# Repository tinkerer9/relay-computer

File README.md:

# Relay Computer
A relay computer that adds or subtracts two 4-bit numbers made for a Capstone project

## How to use
Power the computer with a 5V through the barrel jack on the top-right.

There are nine switches on the bottom left&mdash;these are the inputs.
The four on the top are the A3-A0 inputs, and the four on the bottom are the B3-B0 inputs.

On the the switch on the middle-right is the additon-subtraction selector.
Switch it up to add the two numbers, and down to subtract them.

## Bill of materials
Here is the BOM (bill of materials) for one of the computer, with links.
Prices are included (shipping not included) but always subject to change.

| Item | Variant | Quantity | Link | Price |
| :-: | :-: | :-: | :-: | :-: |
| Relays *(100x)* | SRD-05VDC-SLC | 20 | [AliExpress](https://www.aliexpress.us/item/3256805988664644.html) | $19.27 |
| Diodes *(100x)* | 1N4007 | 28 | [Amazon](https://www.amazon.com/dp/B0FC2CQF24) | $5.99 |
| LEDs | *red, 5mm* | 33 | | |
| Switches *(10x)* | MTS-102 | 9 | [Amazon](https://www.amazon.com/dp/B0799HC3VY) | $7.99 |
| Barrel Jack | *5.5mm OD* | 1 | | |
| Resistors | 220&ohm; | 33 | | |
| PCB *(5x)* | | 1 | *see [how to order](#how-to-order)* | $15.80 |
| **Total** | | **125** | | **$49.05** |

## How to order
Head to [JLCPCB](https://cart.jlcpcb.com/quote?stencilLayer=2&stencilWidth=140&stencilLength=210&plateType=1) and upload the gerber file at [`production.zip`](https://github.com/tinkerer9/relay-computer/raw/refs/heads/main/production.zip).

Use the default options for customizing your order.
Use this table for reference:

| Option | Selection |
| :-: | :-: |
| Base Material | FR-4 |
| Layers | 2 |
| Dimensions | 210 * 140 mm |
| PCB Qty | *you choose* |
| Product Type | Industrial/Consumer electronics |
| PCB Thickness | 1.6mm |
| PCB Color | *you choose* |

Select a build time and add the PCB to your cart.

For my order, the 5 PCBs costed **$15.80** and the shipping costed **&approx;$30**, plus tarrifs.
I ended up paying **&approx;$50**.
These prices are subject to change.

## Questions
For any questions about this project, feel free to create a [new issue](https://github.com/tinkerer9/relay-computer/issues/new) on this repository.

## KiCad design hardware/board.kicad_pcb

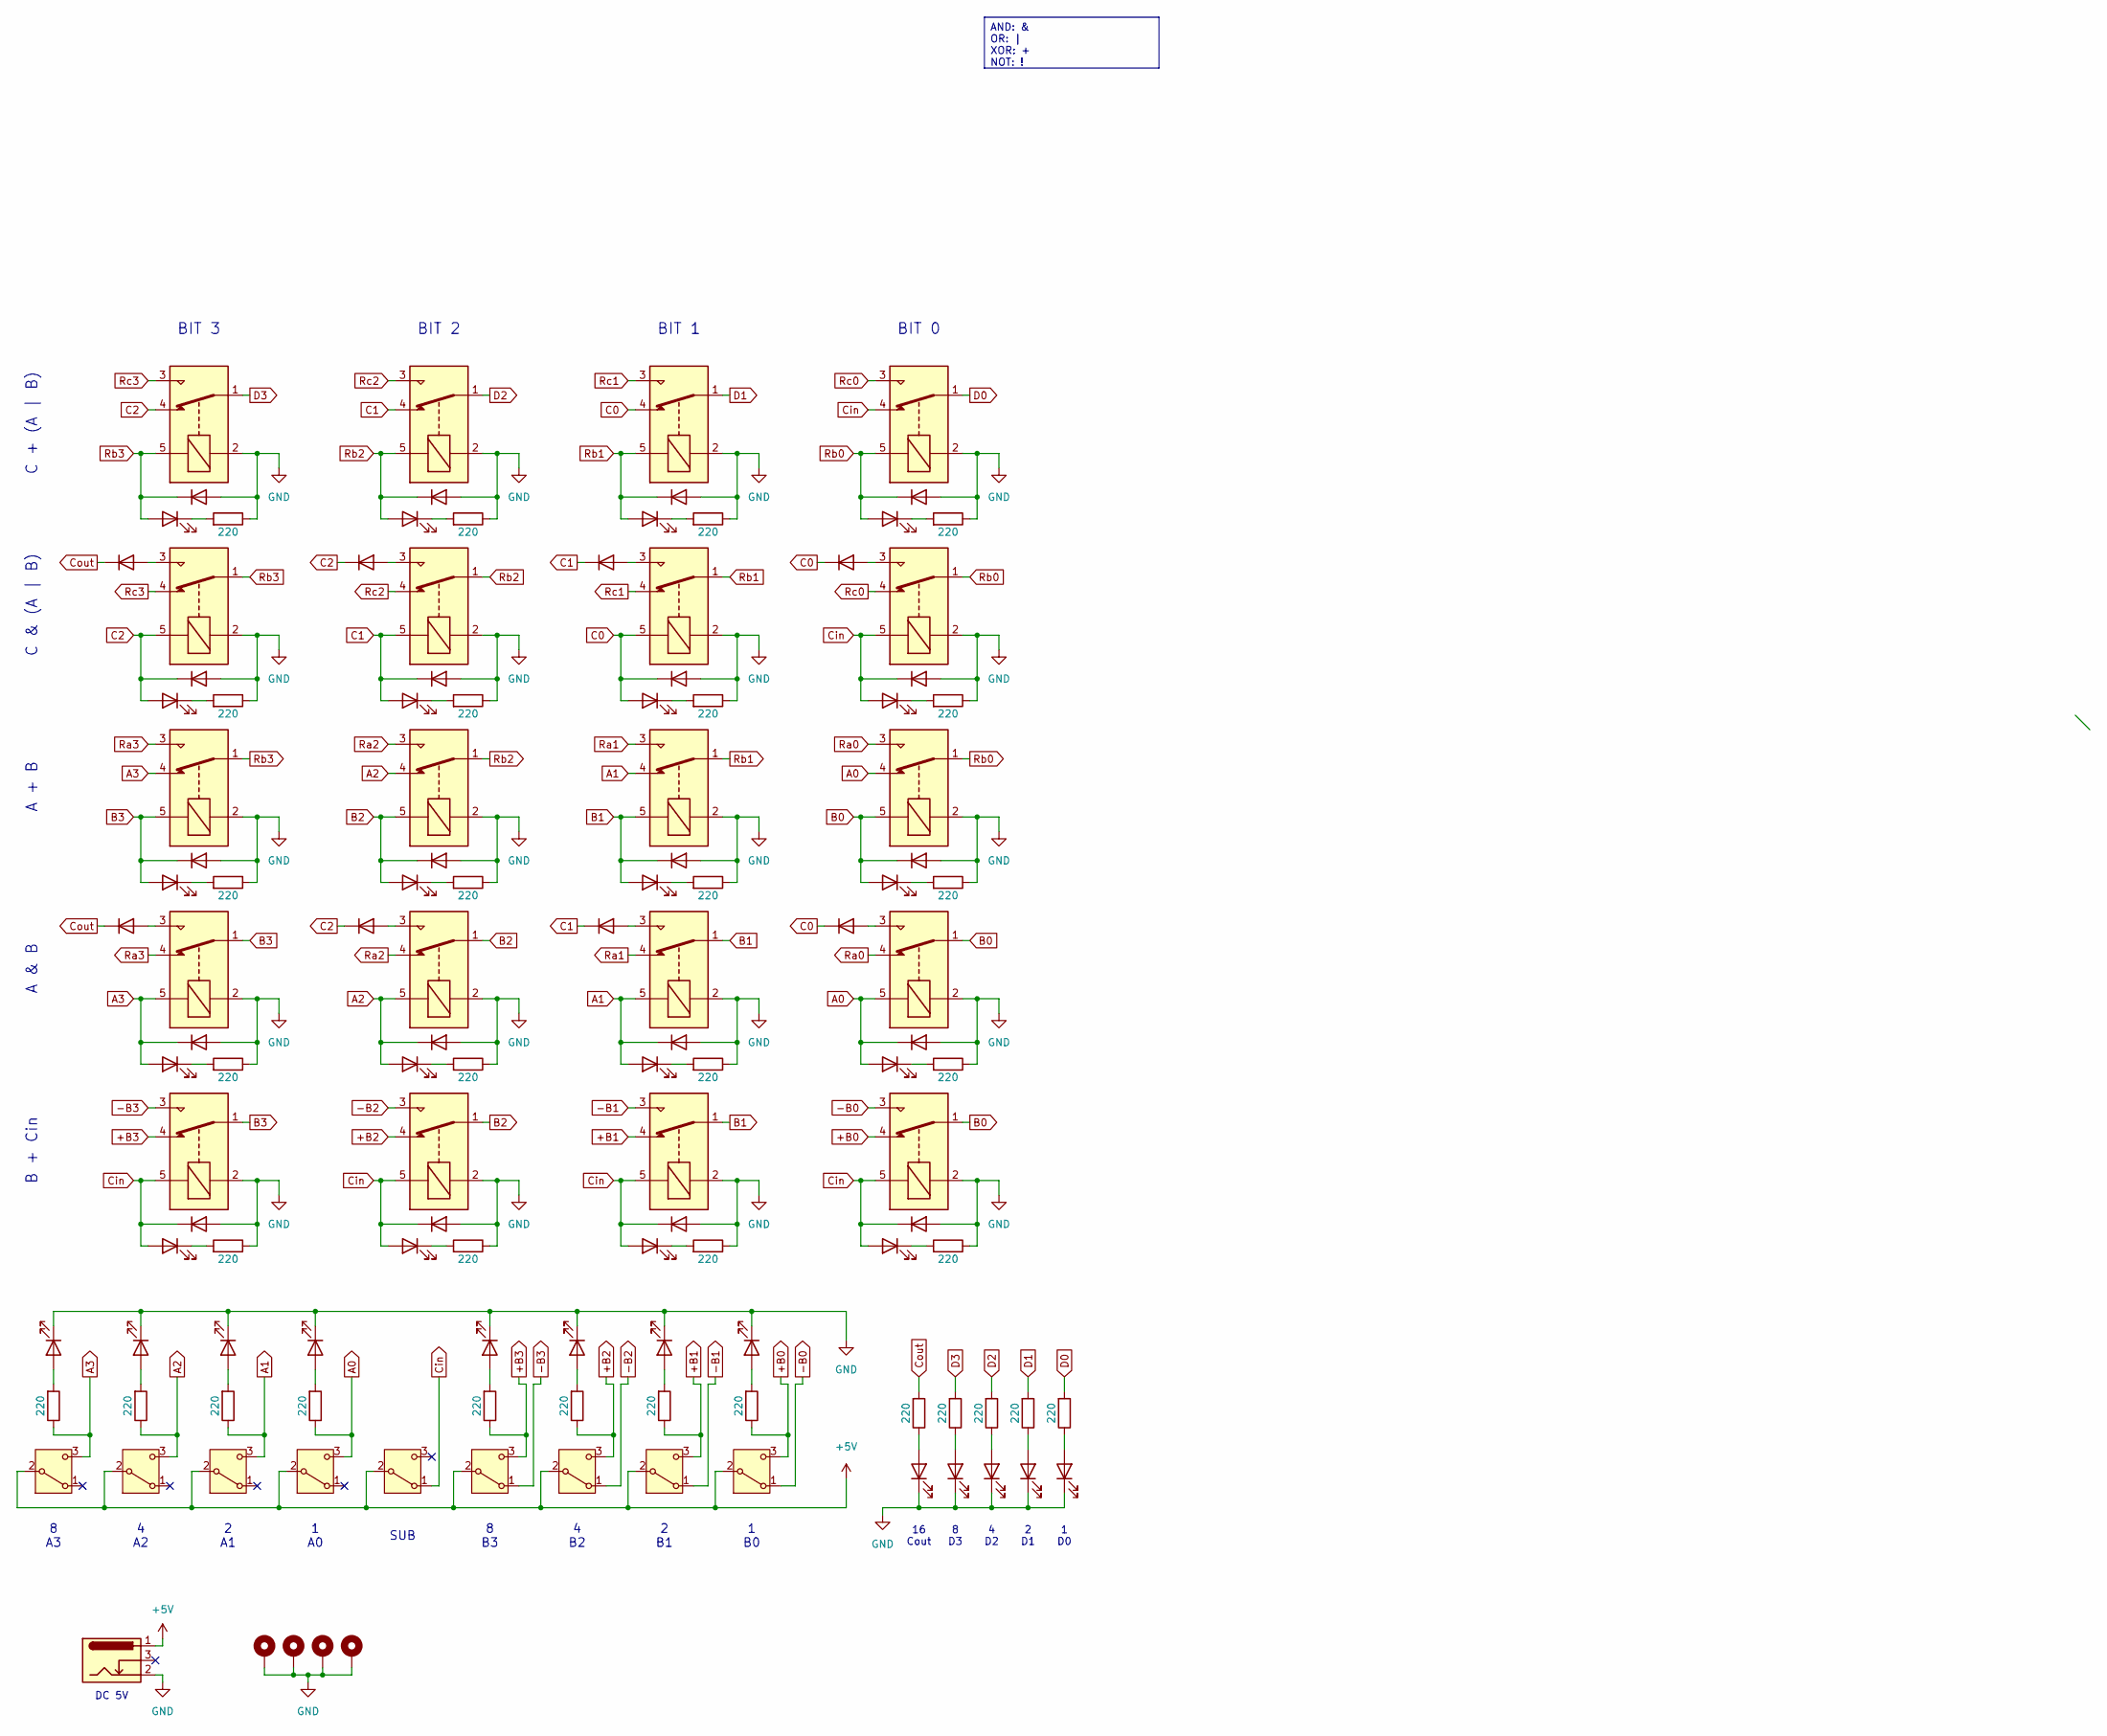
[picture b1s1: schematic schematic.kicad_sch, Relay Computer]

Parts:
D1, D2, D3, D4, D9, D10, D11, D12, D13, D14, D15, D16, D21, D22, D23, D24, D29, D30, D31, D32, D33, D34, D35, D36, D41, D42, D43, D44: 1N4007; D_DO-41_SOD81_P7.62mm_Horizontal
D5, D6, D7, D8, D17, D18, D19, D20, D25, D26, D27, D28, D37, D38, D39, D40, D45, D46, D47, D48, D49, D50, D51, D52, D54, D55, D56, D57, D58, D59, D60, D61, D62: LED; LED_D5.0mm
H1, H2, H3, H4: MountingHole_Pad; MountingHole_4.3mm_M4_Pad
J1: Barrel_Jack_Switch; BarrelJack_Horizontal
K1, K2, K3, K4, K5, K6, K7, K8, K9, K10, K11, K12, K13, K14, K15, K16, K17, K18, K19, K20: SANYOU_SRD_Form_C; Relay_SPDT_SANYOU_SRD_Series_Form_C
R1, R2, R3, R4, R5, R6, R7, R8, R9, R10, R11, R12, R13, R14, R15, R16, R17, R18, R19, R20, R21, R22, R23, R24, R26, R27, R28, R29, R30, R31, R32, R33, R34: 220; R_Axial_DIN0207_L6.3mm_D2.5mm_P10.16mm_Horizontal
SW1, SW2, SW3, SW4, SW5, SW6, SW7, SW8, SW9: SW_SPDT; MTS-102

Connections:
+5V: J1.1, SW1.2 (B), SW2.2 (B), SW3.2 (B), SW4.2 (B), SW5.2 (B), SW6.2 (B), SW7.2 (B), SW8.2 (B), SW9.2 (B)
+B0: K20.4, R29.1, SW9.3 (C)
+B1: K19.4, R28.1, SW8.3 (C)
+B2: K18.4, R27.1, SW7.3 (C)
+B3: K17.4, R26.1, SW6.3 (C)
-B0: K20.3, SW9.1 (A)
-B1: K19.3, SW8.1 (A)
-B2: K18.3, SW7.1 (A)
-B3: K17.3, SW6.1 (A)
A0: D36.1 (K), D40.2 (A), K12.4, K16.5, R24.1, SW4.3 (C)
A1: D35.1 (K), D39.2 (A), K11.4, K15.5, R23.1, SW3.3 (C)
A2: D34.1 (K), D38.2 (A), K10.4, K14.5, R22.1, SW2.3 (C)
A3: D33.1 (K), D37.2 (A), K9.4, K13.5, R21.1, SW1.3 (C)
B0: D24.1 (K), D28.2 (A), K12.5, K16.1, K20.1
B1: D23.1 (K), D27.2 (A), K11.5, K15.1, K19.1
B2: D22.1 (K), D26.2 (A), K10.5, K14.1, K18.1
B3: D21.1 (K), D25.2 (A), K9.5, K13.1, K17.1
C0: D12.1 (K), D15.1 (K), D19.2 (A), D32.1 (K), K3.4, K7.5
C1: D11.1 (K), D14.1 (K), D18.2 (A), D31.1 (K), K2.4, K6.5
C2: D10.1 (K), D13.1 (K), D17.2 (A), D30.1 (K), K1.4, K5.5
Cin: D16.1 (K), D20.2 (A), D41.1 (K), D42.1 (K), D43.1 (K), D44.1 (K), D45.2 (A), D46.2 (A), D47.2 (A), D48.2 (A), K4.4, K8.5, K17.5, K18.5, K19.5, K20.5, SW5.1 (A)
Cout: D9.1 (K), D29.1 (K), R30.2
D0: K4.1, R34.2
D1: K3.1, R33.2
D2: K2.1, R32.2
D3: K1.1, R31.2
GND: D1.2 (A), D2.2 (A), D3.2 (A), D4.2 (A), D13.2 (A), D14.2 (A), D15.2 (A), D16.2 (A), D21.2 (A), D22.2 (A), D23.2 (A), D24.2 (A), D33.2 (A), D34.2 (A), D35.2 (A), D36.2 (A), D41.2 (A), D42.2 (A), D43.2 (A), D44.2 (A), D49.1 (K), D50.1 (K), D51.1 (K), D52.1 (K), D54.1 (K), D55.1 (K), D56.1 (K), D57.1 (K), D58.1 (K), D59.1 (K), D60.1 (K), D61.1 (K), D62.1 (K), H1.1, H2.1, H3.1, H4.1, J1.2, K1.2, K2.2, K3.2, K4.2, K5.2, K6.2, K7.2, K8.2, K9.2, K10.2, K11.2, K12.2, K13.2, K14.2, K15.2, K16.2, K17.2, K18.2, K19.2, K20.2, R1.1, R2.1, R3.1, R4.1, R5.1, R6.1, R7.1, R8.1, R9.1, R10.1, R11.1, R12.1, R13.1, R14.1, R15.1, R16.1, R17.1, R18.1, R19.1, R20.1
unnamed: D5.1 (K), R1.2
unnamed: D6.1 (K), R2.2
unnamed: D7.1 (K), R3.2
unnamed: D8.1 (K), R4.2
unnamed: D9.2 (A), K5.3
unnamed: D10.2 (A), K6.3
unnamed: D11.2 (A), K7.3
unnamed: D12.2 (A), K8.3
unnamed: D17.1 (K), R5.2
unnamed: D18.1 (K), R6.2
unnamed: D19.1 (K), R7.2
unnamed: D20.1 (K), R8.2
unnamed: D25.1 (K), R9.2
unnamed: D26.1 (K), R10.2
unnamed: D27.1 (K), R11.2
unnamed: D28.1 (K), R12.2
unnamed: D29.2 (A), K13.3
unnamed: D30.2 (A), K14.3
unnamed: D31.2 (A), K15.3
unnamed: D32.2 (A), K16.3
unnamed: D37.1 (K), R13.2
unnamed: D38.1 (K), R14.2
unnamed: D39.1 (K), R15.2
unnamed: D40.1 (K), R16.2
unnamed: D45.1 (K), R17.2
unnamed: D46.1 (K), R18.2
unnamed: D47.1 (K), R19.2
unnamed: D48.1 (K), R20.2
unnamed: D49.2 (A), R21.2
unnamed: D50.2 (A), R22.2
unnamed: D51.2 (A), R23.2
unnamed: D52.2 (A), R24.2
unnamed: D54.2 (A), R26.2
unnamed: D55.2 (A), R27.2
unnamed: D56.2 (A), R28.2
unnamed: D57.2 (A), R29.2
unnamed: D58.2 (A), R30.1
unnamed: D59.2 (A), R31.1
unnamed: D60.2 (A), R32.1
unnamed: D61.2 (A), R33.1
unnamed: D62.2 (A), R34.1
Ra0: K12.3, K16.4
Ra1: K11.3, K15.4
Ra2: K10.3, K14.4
Ra3: K9.3, K13.4
Rb0: D4.1 (K), D8.2 (A), K4.5, K8.1, K12.1
Rb1: D3.1 (K), D7.2 (A), K3.5, K7.1, K11.1
Rb2: D2.1 (K), D6.2 (A), K2.5, K6.1, K10.1
Rb3: D1.1 (K), D5.2 (A), K1.5, K5.1, K9.1
Rc0: K4.3, K8.4
Rc1: K3.3, K7.4
Rc2: K2.3, K6.4
Rc3: K1.3, K5.4

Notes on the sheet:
BIT 3
2 B1
A & B
BIT 0
C + (A | B)
BIT 1
4 B2
8 D3
16 Cout
1 A0
1 B0
A + B
4 A2
DC 5V
8 B3
4 D2
2 A1
SUB
2 D1
C & (A | B)
8 A3
B + Cin
1 D0
BIT 2
AND: & OR: | XOR: + NOT: !

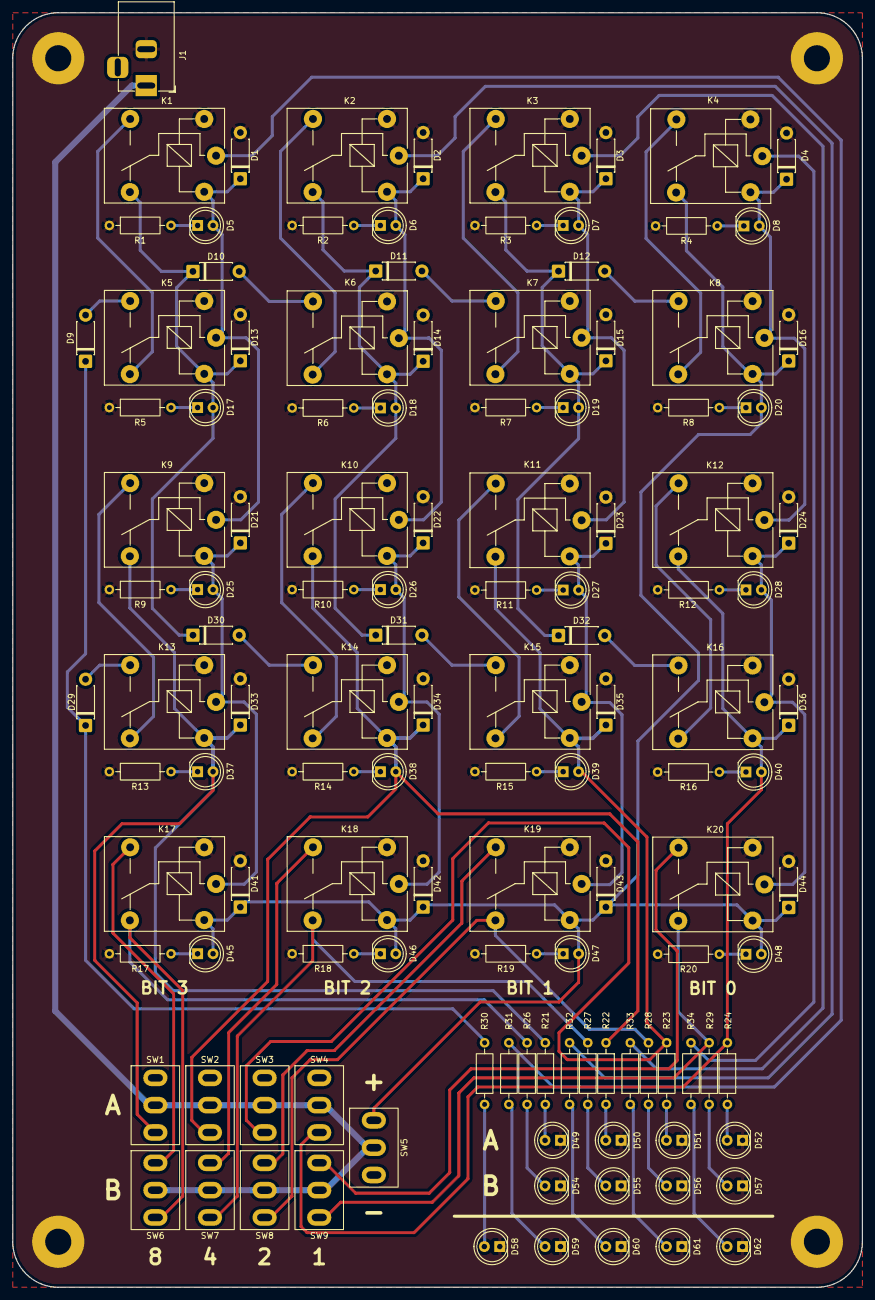
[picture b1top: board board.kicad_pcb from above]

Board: 2 copper layers, 140.0 x 210.0 mm, 128 parts (0 on the bottom side), 80 nets.

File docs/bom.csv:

"Reference","Qty","Value","Footprint"
"D1-D4;D9-D16;D21-D24;D29-D36;D41-D44","28","1N4007","Diode_THT:D_DO-41_SOD81_P7.62mm_Horizontal"
"D5-D8;D17-D20;D25-D28;D37-D40;D45-D52;D54-D62","33","LED","LED_THT:LED_D5.0mm"
"H1-H4","4","MountingHole_Pad","MountingHole:MountingHole_4.3mm_M4_Pad"
"J1","1","Barrel_Jack_Switch","Connector_BarrelJack:BarrelJack_Horizontal"
"K1-K20","20","SANYOU_SRD_Form_C","Relay_THT:Relay_SPDT_SANYOU_SRD_Series_Form_C"
"R1-R24;R26-R34","33","220","Resistor_THT:R_Axial_DIN0207_L6.3mm_D2.5mm_P10.16mm_Horizontal"
"SW1-SW9","9","SW_SPDT","Toggle_Switch:MTS-102"

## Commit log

2026-05-05 Add .gitignore for KiCad
2026-05-05 not done yet...
2026-05-05 update table
2026-05-05 Add files
2026-05-05 how to use, how to order
2026-05-05 add BOM
2026-05-06 Fix syntax typo
2026-05-07 Fix formatting of PCB ordering note in README
